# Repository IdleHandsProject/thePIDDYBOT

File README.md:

# thePIDDYBOT
PIDDYBOT is an Open Source Balancing Robot with the aim of teaching PID control.

Check out the Video:

Do not populate F1 or D6

**I somehow lost the original EagleCAD files for the PIDDYBOT. I still have the .BRD file, but no schem. I have plans to update the design with the SAMD21 instead of the Atmel, and it will be done in KiCad not Eagle. Stay Tuned**

There is an instructables on building the PIDDYBOT which contains the parts needed:
https://www.instructables.com/id/PIDDYBOT-DIY-Arduino-Balancing-Robot/

The FindChips(BOM):
https://www.findchips.com/org/10-open-hardware/list/46854-the-piddybot-encoders?sort=created&order=desc

HaD.io: https://hackaday.io/project/27330-the-piddybot

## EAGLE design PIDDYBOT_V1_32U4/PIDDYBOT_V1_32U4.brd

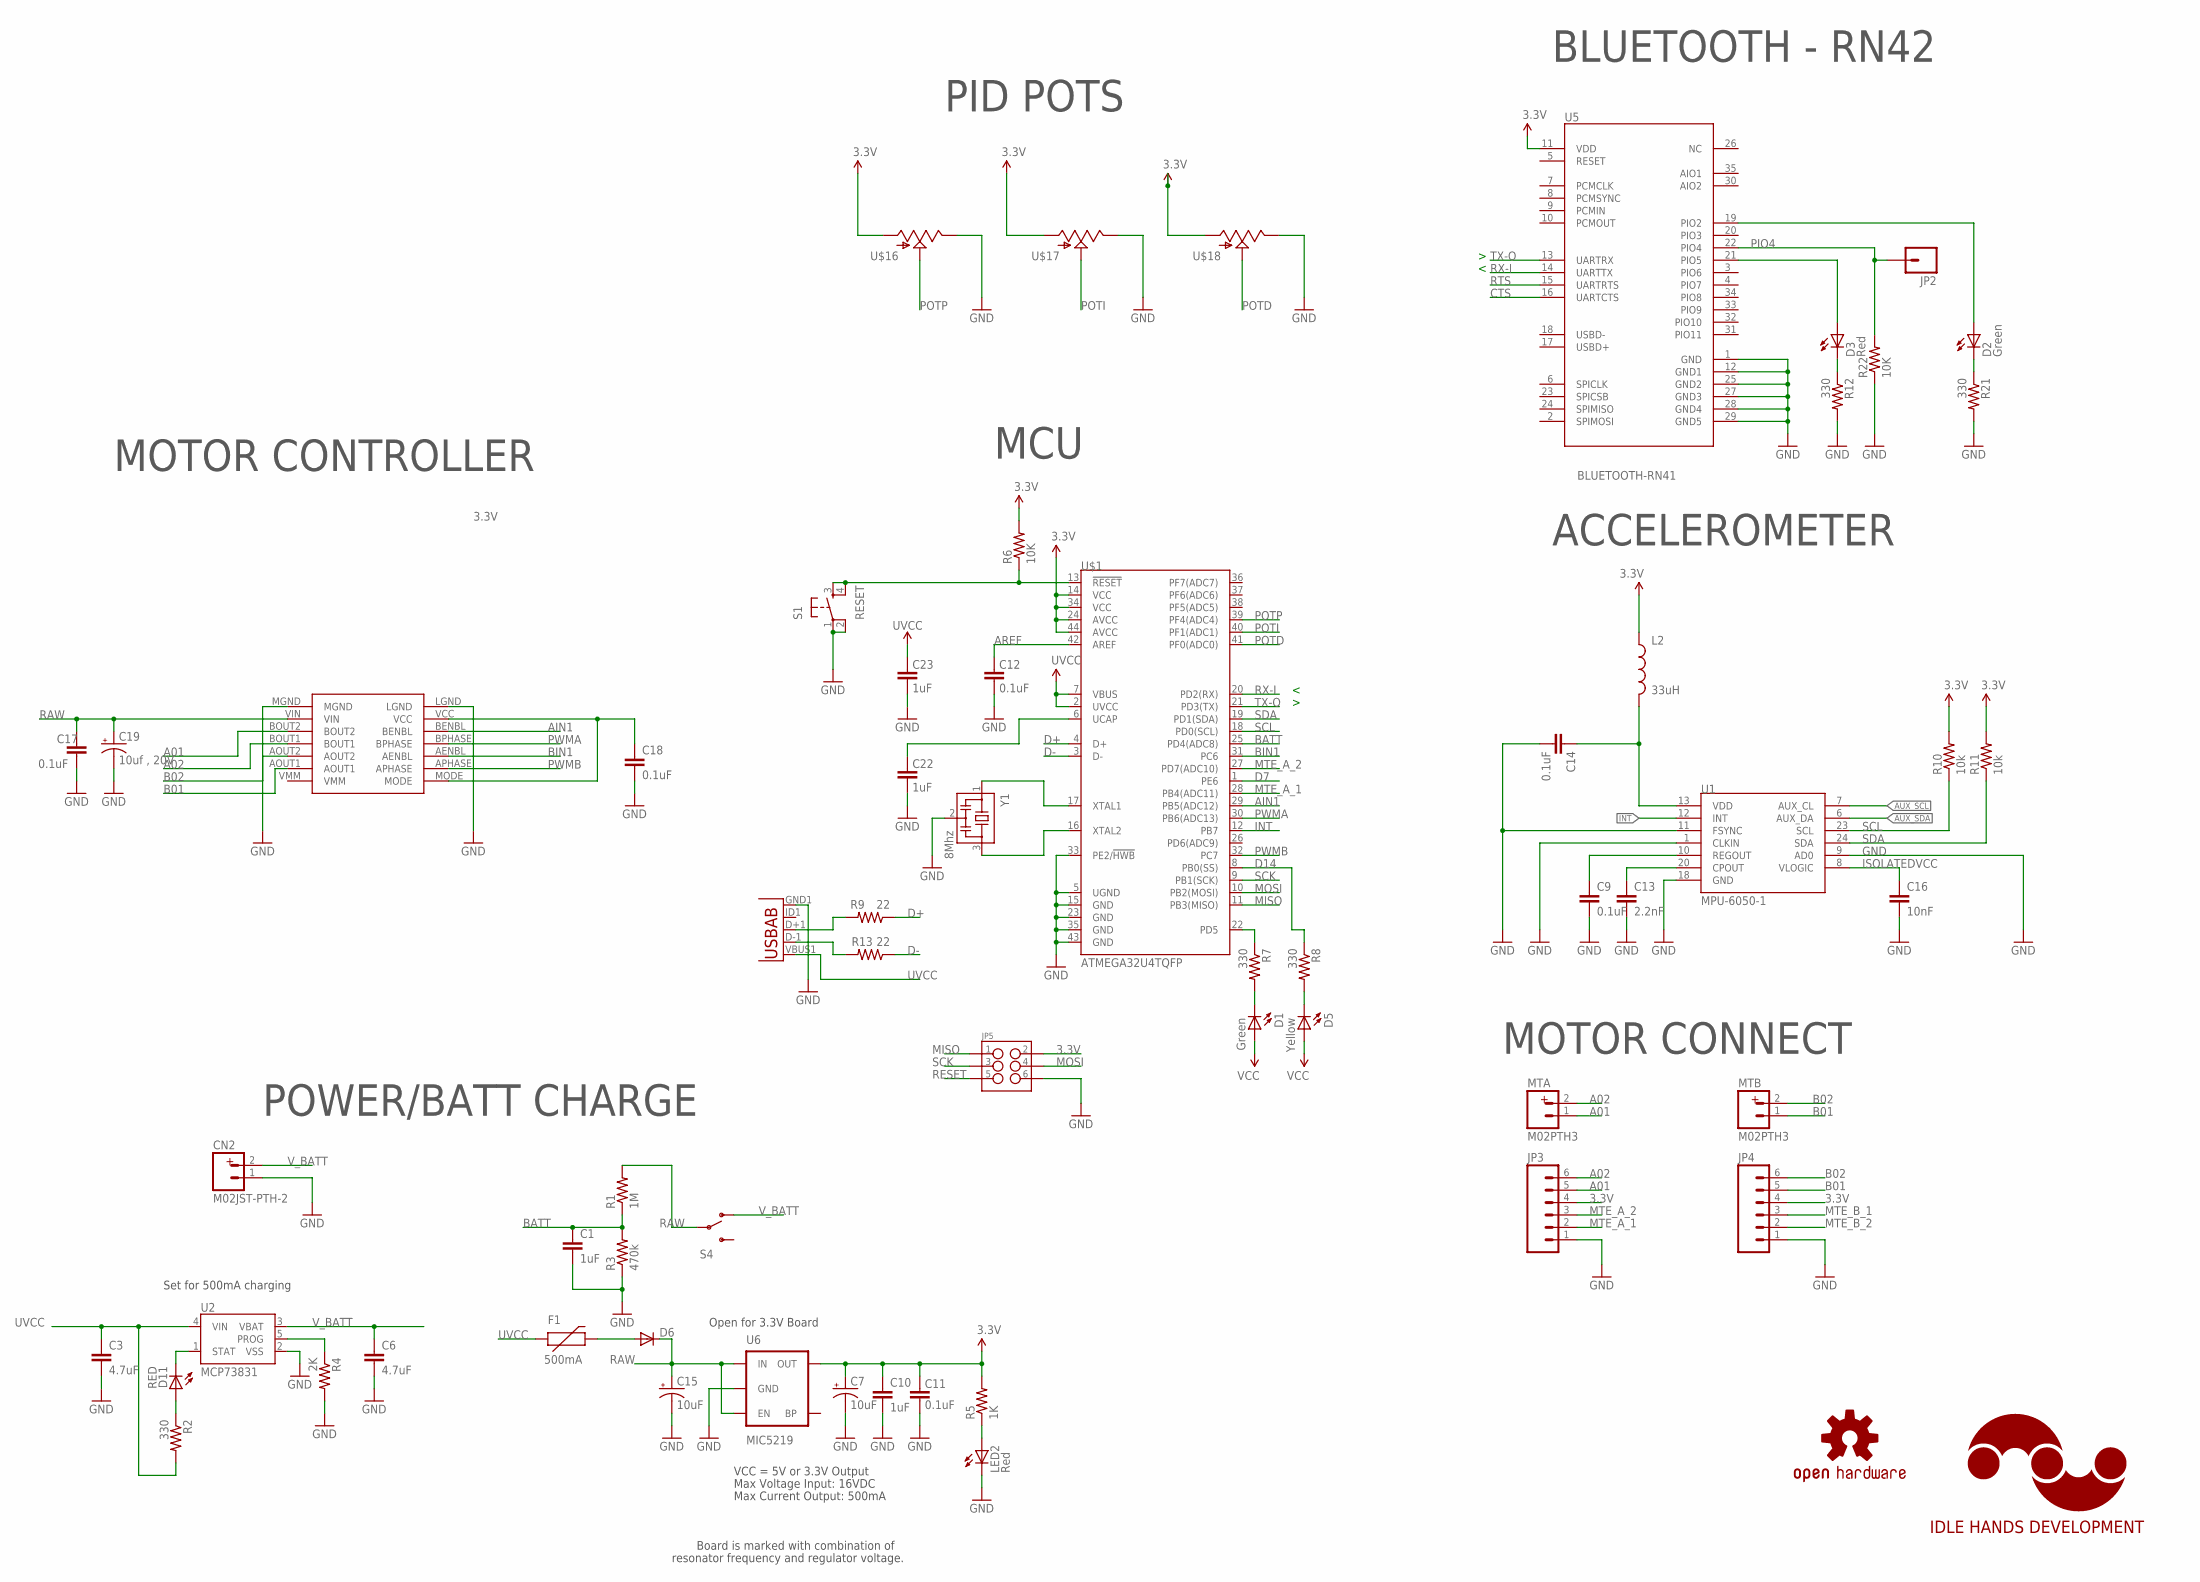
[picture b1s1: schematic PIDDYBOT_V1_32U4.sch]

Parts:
C1, C10, C22, C23: 1uF; 0603-CAP
C3, C6: 4.7uF; 0603-CAP
C7, C15: 10uF; EIA3216
C9, C11, C12, C14, C17, C18: 0.1uF; 0603-CAP
C13: 2.2nF; 0603-CAP
C16: 10nF; 0603-CAP
C19: 10uf , 20V; EIA3528
CN2: M02JST-PTH-2; JST-2-PTH
D1, D2: Green; LED-0603
D3: Red; LED-0603
D5: Yellow; LED-0603
D6: DIODESOD; SOD-323
D11: RED; LED-0603
F1: 500mA; PTC-1206
JP2: M01SMDNS; 1X01NS
JP3, JP4: M06SMD-1MM; 1X06-1MM
JP5: M03X2NO_SILK; 2X3-NS
L2: 33uH; C0402
LED2: Red; LED-0603
LOGO1: IDLEHANDS_LOGOL; IHD-LOGO-L
LOGO2: OSHW-LOGOM; OSHW-LOGO-M
MTA: M02PTH3; 1X02_LONGPADS
MTB: M02PTH3; 1X02_LONGPADS
R1: 1M; 0603-RES
R2, R7, R8, R12, R21: 330; 0603-RES
R3: 470k; 0603-RES
R4: 2K; 0603-RES
R5: 1K; 0603-RES
R6, R22: 10K; 0603-RES
R9, R13: 22; 0603-RES
R10, R11: 10k; 0603-RES
S1: RESET; TACTILE_SWITCH_SMD
S4: SWITCH-SPDTPTH; SWITCH-SPDT
U1: MPU-6050-1; QFN-24-4MM2
U2: MCP73831; SOT23-5
U5: BLUETOOTH-RN41; RN41
U6: MIC5219; SOT23-5
U$1: ATMEGA32U4TQFP; SPARKFUN-DIGITALIC_TQFP44
U$2: POLOLU_MOTOR_DRV8835THROUGHHOLE; POLOLU_MOTOR_DRV_DRV8835
U$16, U$17, U$18: POT; ALPS_POT
X2: USB-ABIN&OUT; USB-AB-MICRO-SMD-V03-IN&OUT
Y1: 8Mhz; CSTCR6M

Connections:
3.3V: C7.A (+), C10.1, C11.2, C18.1, D1.A, D5.A, JP3.4, JP4.4, JP5.2, L2.1, R5.2, R6.2, R10.2, R11.2, U5.11 (VDD), U6.5 (OUT), U$1.14 (VCC), U$1.24 (AVCC), U$1.34 (VCC), U$1.44 (AVCC), U$2.MODE, U$16.P$3 (A), U$17.P$3 (A), U$18.P$3 (A)
A01: JP3.5, MTA.1, U$2.BOUT2
A02: JP3.6, MTA.2, U$2.BOUT1
AIN1: U$1.29 (PB5(ADC12)), U$2.BENBL
AREF: C12.2, U$1.42 (AREF)
AUX_SCL: U1.7 (AUX_CL)
AUX_SDA: U1.6 (AUX_DA)
B01: JP4.5, MTB.1, U$2.AOUT1
B02: JP4.6, MTB.2, U$2.AOUT2
BATT: C1.1, R1.1, R3.2, U$1.25 (PD4(ADC8))
BIN1: U$1.31 (PC6), U$2.AENBL
CTS: U5.16 (UARTCTS)
D1: D3.C, R12.1
D2: D2.C, R21.1
D7: U$1.1 (PE6)
D14: R8.1, U$1.8 (PB0(SS))
D+: R9.1, U$1.4 (D+)
D-: R13.1, U$1.3 (D-)
GND: C1.2, C3.2, C6.2, C7.C (-), C9.2, C10.2, C11.1, C12.1, C13.2, C14.2, C15.C (-), C16.2, C17.2, C18.2, C19.C (-), C22.1, C23.1, CN2.1, JP3.1, JP4.1, JP5.6, LED2.C, R3.1, R4.2, R12.2, R21.2, R22.1, S1.1, S1.2, U1.1 (CLKIN), U1.9 (AD0), U1.11 (FSYNC), U1.18 (GND), U2.2 (VSS), U5.1 (GND), U5.12 (GND1), U5.25 (GND2), U5.27 (GND3), U5.28 (GND4), U5.29 (GND5), U6.2 (GND), U$1.5 (UGND), U$1.15 (GND), U$1.23 (GND), U$1.33 (PE2/!HWB), U$1.35 (GND), U$1.43 (GND), U$2.LGND, U$2.MGND, U$16.P$1 (E), U$17.P$1 (E), U$18.P$1 (E), X2.GND1 (GND), Y1.2
INT: U1.12 (INT), U$1.12 (PB7)
ISOLATEDVCC: C14.1, C16.1, L2.2, U1.8 (VLOGIC), U1.13 (VDD)
MISO: JP5.1, U$1.11 (PB3(MISO))
MOSI: JP5.4, U$1.10 (PB2(MOSI))
MTE_A_1: JP3.2, U$1.28 (PB4(ADC11))
MTE_A_2: JP3.3, U$1.27 (PD7(ADC10))
MTE_B_1: JP4.3
MTE_B_2: JP4.2
unnamed: U$1.17 (XTAL1), Y1.1
unnamed: U$1.16 (XTAL2), Y1.3
unnamed: D6.2 (A), F1.2
unnamed: C13.1, U1.20 (CPOUT)
unnamed: C9.1, U1.10 (REGOUT)
unnamed: D3.A, U5.21 (PIO5)
unnamed: D2.A, U5.19 (PIO2)
unnamed: D11.A, R2.1
unnamed: C22.2, U$1.6 (UCAP)
unnamed: R13.2, X2.D-1 (D-)
unnamed: R9.2, X2.D+1 (D+)
unnamed: D5.C, R8.2
unnamed: D1.C, R7.2
unnamed: LED2.A, R5.1
PIO4: JP2.1, R22.2, U5.22 (PIO4)
POTD: U$1.41 (PF0(ADC0)), U$18.P$2 (S)
POTI: U$1.40 (PF1(ADC1)), U$17.P$2 (S)
POTP: U$1.39 (PF4(ADC4)), U$16.P$2 (S)
PROG: R4.1, U2.5 (PROG)
PWMA: U$1.30 (PB6(ADC13)), U$2.BPHASE
PWMB: U$1.32 (PC7), U$2.APHASE
RAW: C15.A (+), C17.1, C19.A (+), D6.1 (C), R1.2, S4.2, U6.1 (IN), U6.3 (EN), U$2.VIN
RESET: JP5.5, R6.1, S1.3, S1.4, U$1.13 (!RESET)
RTS: U5.15 (UARTRTS)
RX-I: U5.14 (UARTTX), U$1.20 (PD2(RX))
SCK: JP5.3, U$1.9 (PB1(SCK))
SCL: R10.1, U1.23 (SCL), U$1.18 (PD0(SCL))
SDA: R11.1, U1.24 (SDA), U$1.19 (PD1(SDA))
STAT: D11.C, U2.1 (STAT)
TX-O: U5.13 (UARTRX), U$1.21 (PD3(TX))
TXLED: R7.1, U$1.22 (PD5)
UVCC: C3.1, C23.2, F1.1, R2.2, U2.4 (VIN), U$1.2 (UVCC), U$1.7 (VBUS), X2.VBUS1 (VBUS)
V_BATT: C6.1, CN2.2, S4.1 (O), U2.3 (VBAT)

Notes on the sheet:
Set for 500mA charging
Max Voltage Input: 16VDC
Max Current Output: 500mA
Board is marked with combination of
resonator frequency and regulator voltage.
VCC = 5V or 3.3V Output
Open for 3.3V Board
MOTOR CONTROLLER
MCU
PID POTS
BLUETOOTH - RN42
ACCELEROMETER
MOTOR CONNECT
POWER/BATT CHARGE

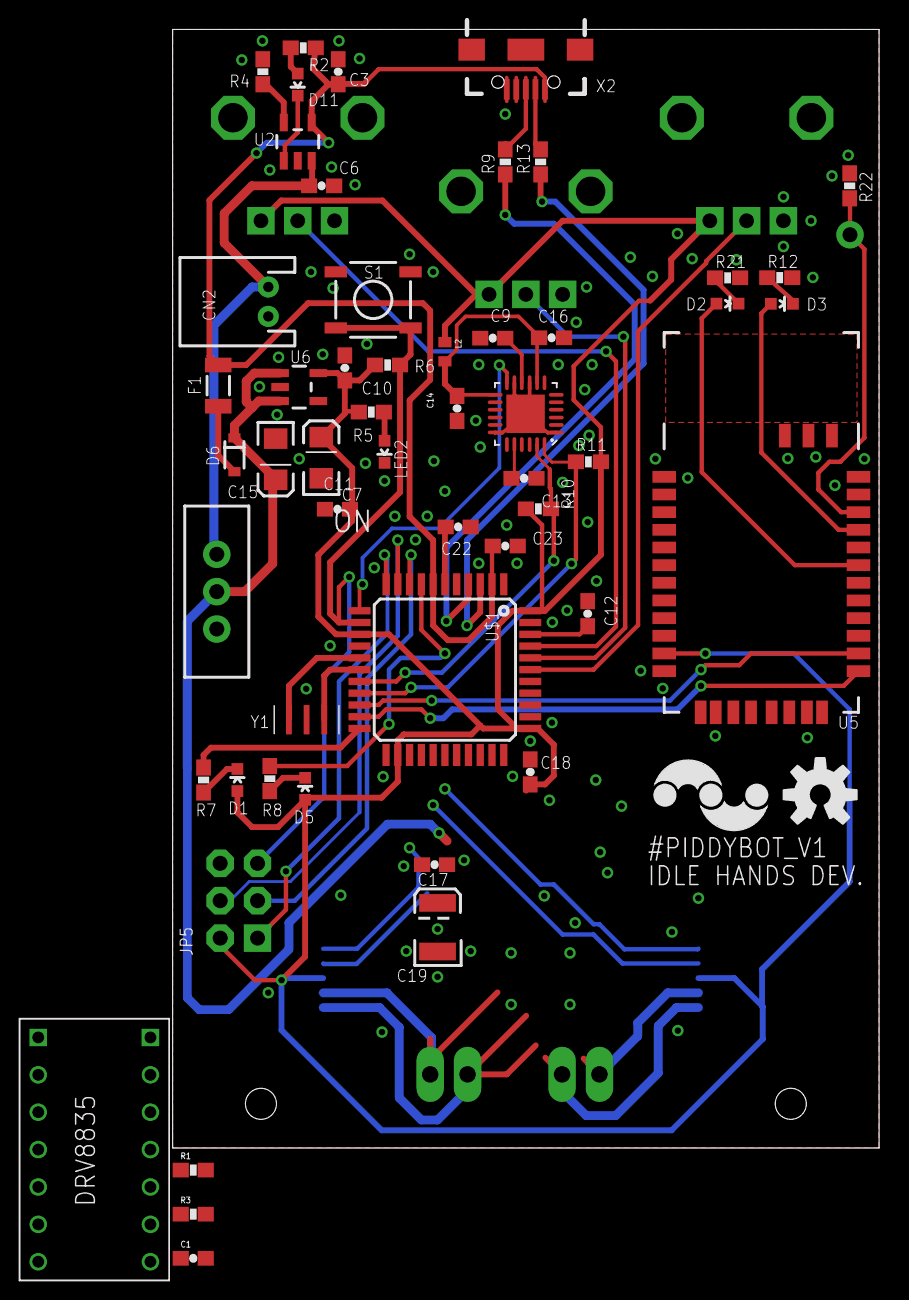
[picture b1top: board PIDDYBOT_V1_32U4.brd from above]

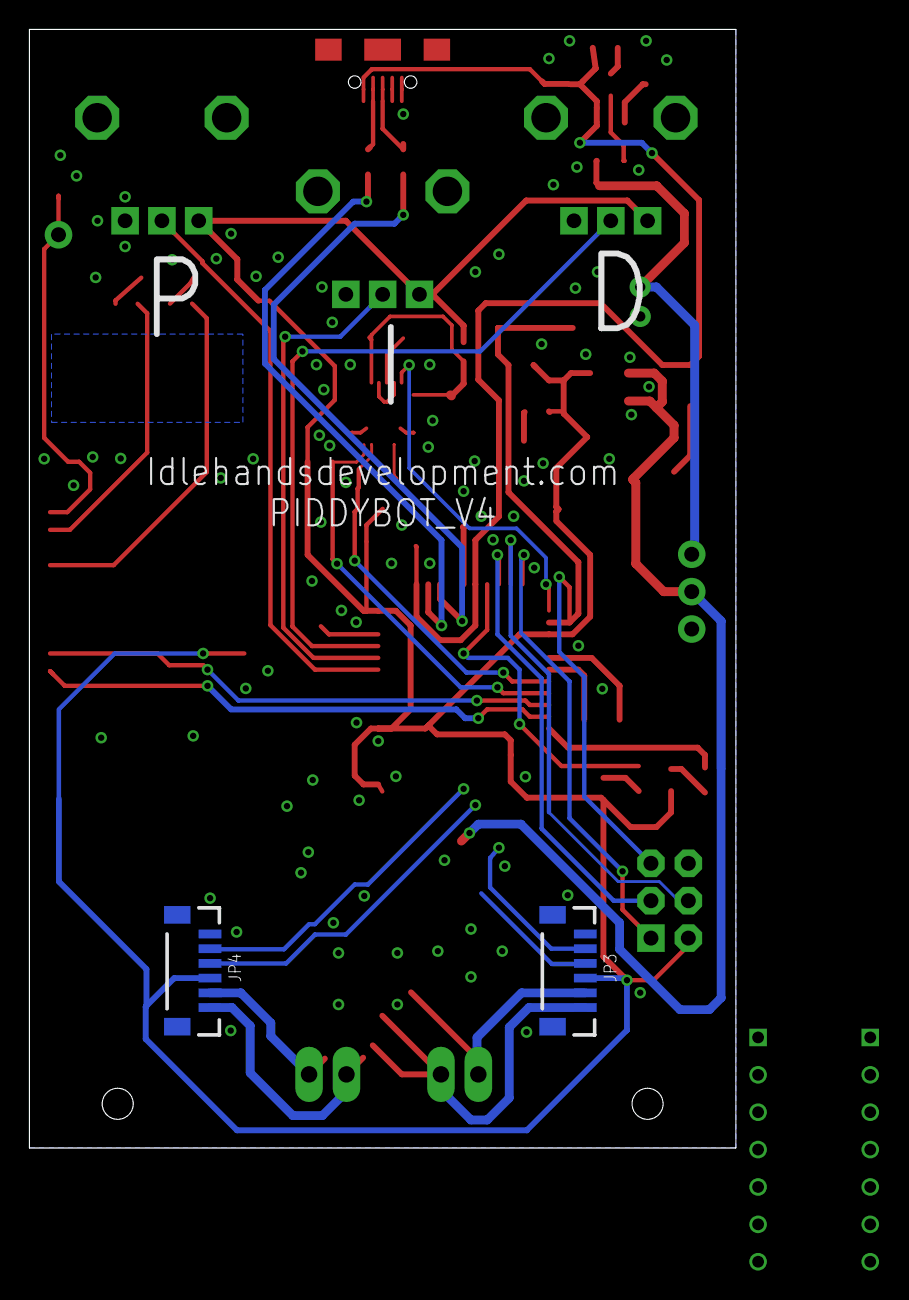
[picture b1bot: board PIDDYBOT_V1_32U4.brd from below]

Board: 2 copper layers, 48.0 x 76.0 mm, 63 parts (5 on the bottom side), 53 nets.

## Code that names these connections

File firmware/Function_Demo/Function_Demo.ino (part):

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int B = 2;

//Motor A
int PWMA = 10; //Speed control
int AIN1 = 9; //Direction

//Motor B
int PWMB = 13; //Speed control
int BIN1 = 5; //Direction

// Potentiometers
static int pot1 = A3;
static int pot2 = A4;
static int pot3 = A5;

static int BATT = A6;

//float distancecount = 0;
float correction = -10;
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
void setup() {
  //MOTOR SETUP
  pinMode(PWMA, OUTPUT);
  pinMode(AIN1, OUTPUT);
  pinMode(PWMB, OUTPUT);
  pinMode(BIN1, OUTPUT);
  pinMode(BATT, INPUT);

  // Serial Connection
  Serial.begin(38400);
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  */

  if (motor == 1) {
    digitalWrite(AIN1, inPin1);
    analogWrite(PWMA, leftspeed);
  }
  else {
    digitalWrite(BIN1, inPin1);
    analogWrite(PWMB, rightspeed);
  }
}
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
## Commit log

2017-09-17 added firmware
2017-09-17 updated body
2017-09-21 Program Improvements(EEPROM etc.)
2017-09-21 added updated BOM
2017-09-21 renamed
2017-09-21 Quick Start Guide
2017-10-08 Added SCH file, updated firmware
2017-10-09 Added function demo

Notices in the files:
parts and their libraries:
SparkFun-Connectors: Licensing: CC v3.0 Share-Alike You are welcome to use this library for commercial purposes.
